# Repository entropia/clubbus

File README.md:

EDEN
====

EDEN is Entropia's home automation project. More information can be found in our [wiki](https://entropia.de/Clubbus).

Stuff will be publicly released here when it's ready.

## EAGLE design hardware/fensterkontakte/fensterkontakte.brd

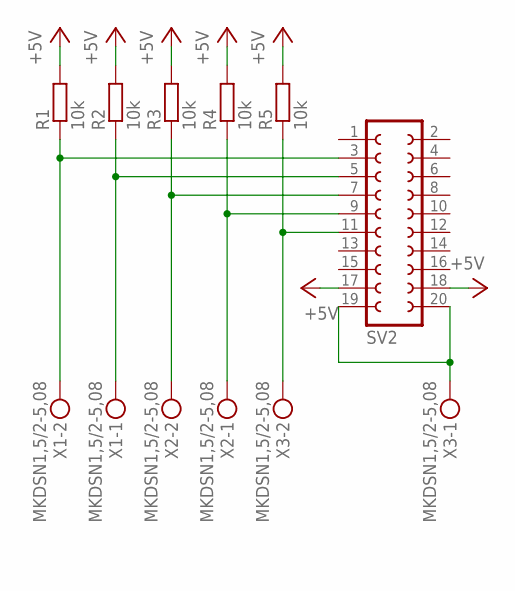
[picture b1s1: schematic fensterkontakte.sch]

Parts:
R1, R2, R3, R4, R5: 10k; M0805
SV2: FE10-2
X1, X2, X3: MKDSN1,5/2-5,08

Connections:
+5V: R1.2, R2.2, R3.2, R4.2, R5.2, SV2.17, SV2.18
GND: SV2.19, SV2.20, X3.1
unnamed: R1.1, SV2.3, X1.2
unnamed: R2.1, SV2.5, X1.1
unnamed: R3.1, SV2.7, X2.2
unnamed: R4.1, SV2.9, X2.1
unnamed: R5.1, SV2.11, X3.2

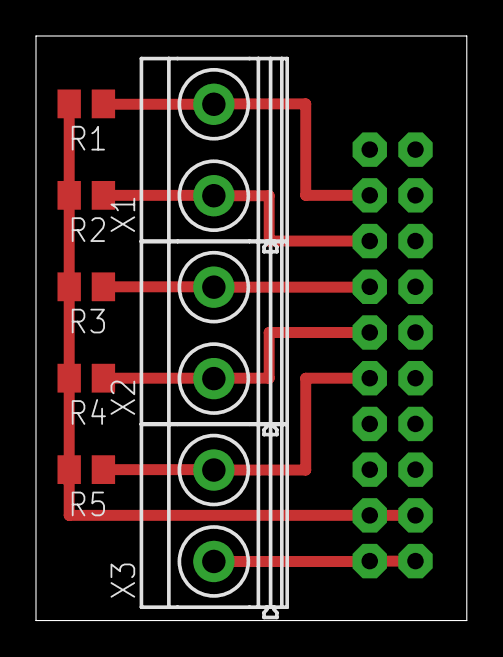
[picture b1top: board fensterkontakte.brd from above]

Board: 2 copper layers, 23.9 x 32.5 mm, 9 parts (1 on the bottom side), 7 nets.

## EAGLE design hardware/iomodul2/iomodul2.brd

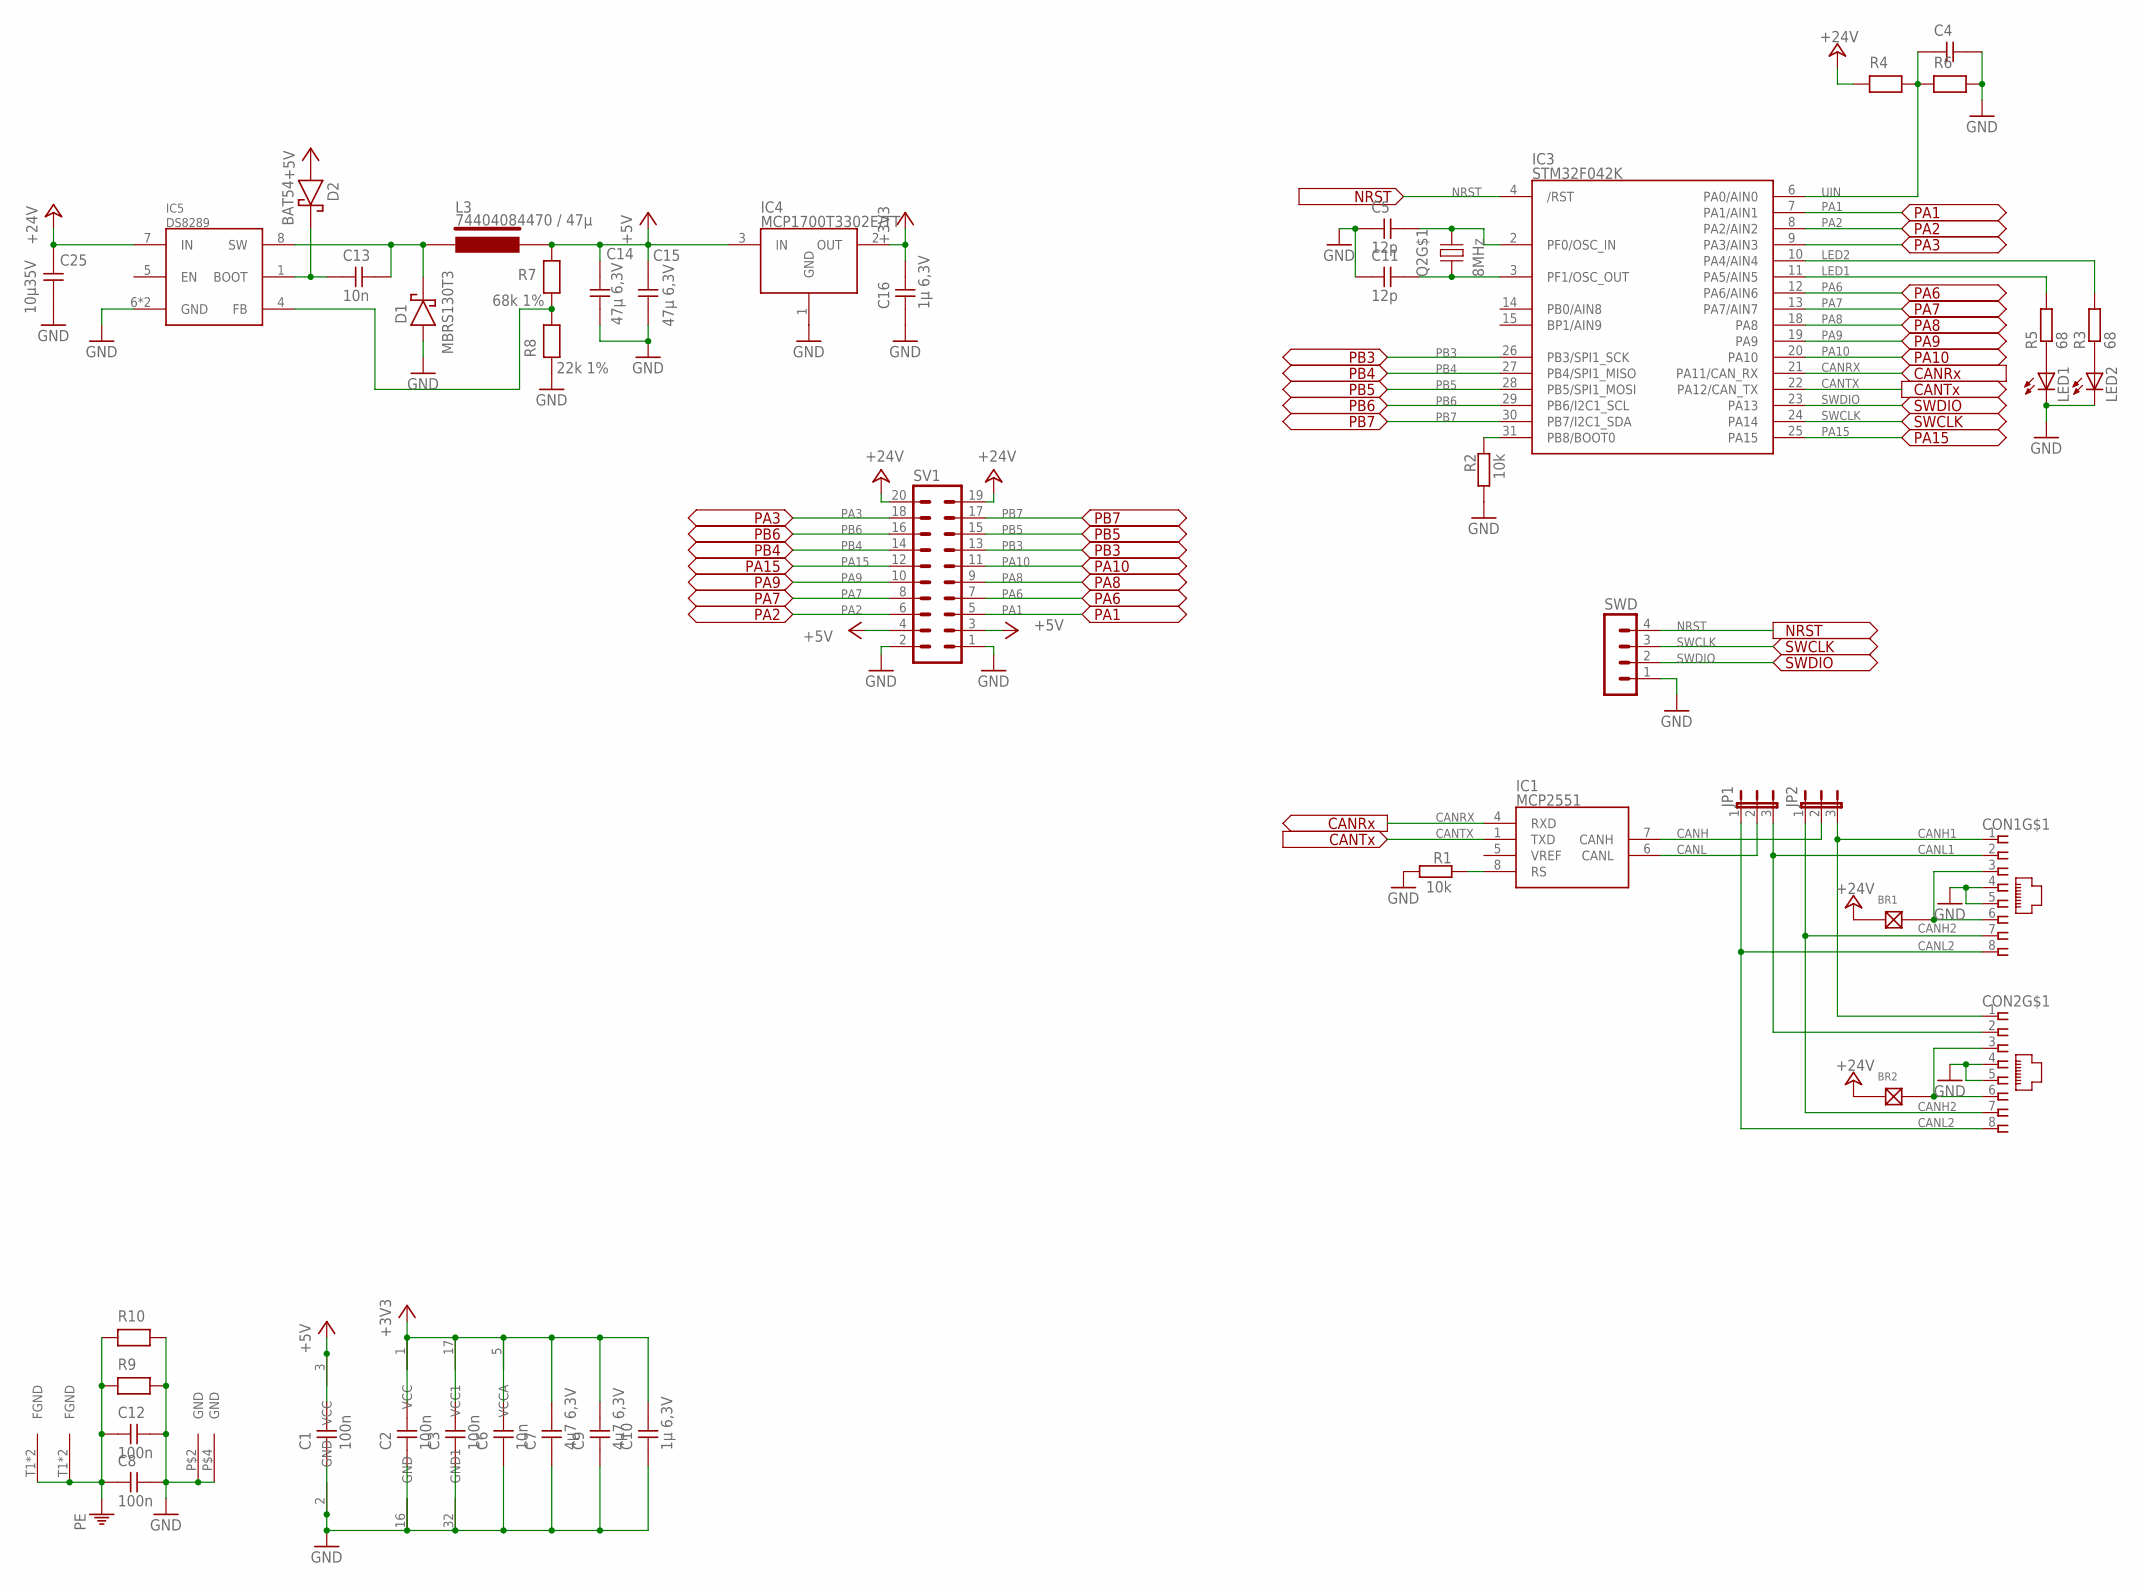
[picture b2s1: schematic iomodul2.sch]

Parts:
BR1, BR2: LÖTBRÜCKE-S; LÖTBRÜCKE
C1, C2, C3, C8, C12: 100n; 0603REFLOW
C4: CAP0603R; 0603REFLOW
C5, C11: 12p; 0603REFLOW
C6, C13: 10n; 0603REFLOW
C7, C9: 4µ7 6,3V; 0603REFLOW
C10, C16: 1µ 6,3V; 0603REFLOW
C14, C15: 47µ 6,3V; 1210
C25: 10µ35V; 1206
CON1, CON2: MEBP_8-8G; MEBP
D1: MBRS130T3; SMB
D2: BAT54; SOT23/32
IC1: MCP2551; SO-8
IC3: STM32F042K; LQFP32
IC4: MCP1700T3302E/TT; SOT23
IC5: DS8289; SO8-POWERPAD
JP1, JP2: JP2E; JP2
L3: 74404084470 / 47µ; WE-LQS
LED1, LED2: LEDCHIPLED_0603; CHIPLED_0603
Q2: 8MHz; MT-CRYSTAL
R1, R2: 10k; R0603
R3, R5: 68; R0603
R4, R6, R9, R10: RES0603R; 0603REFLOW
R7: 68k 1%; 0603REFLOW
R8: 22k 1%; 0603REFLOW
SV1: MA10-2
SWD: MA04-1

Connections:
+3V3: C2.2, C3.2, C6.2, C7.2, C9.2, C10.2, C16.2, IC3.1 (VCC), IC3.5 (VCCA), IC3.17 (VCC1), IC4.2 (OUT)
+5V: C1.2, C14.2, C15.2, D2.1 (A), IC1.3 (VCC), IC4.3 (IN), L3.P$2, R7.2, SV1.3, SV1.4
+24V: BR1.1, BR2.1, C25.2, IC5.7 (IN), R4.1, SV1.19, SV1.20
CANH: IC1.7 (CANH), JP2.2
CANH1: CON1.1, CON2.1, JP2.3
CANH2: CON1.7, CON2.7, JP2.1
CANL: IC1.6 (CANL), JP1.2
CANL1: CON1.2, CON2.2, JP1.3
CANL2: CON1.8, CON2.8, JP1.1
CANRX: IC1.4 (RXD), IC3.21 (PA11/CAN_RX)
CANTX: IC1.1 (TXD), IC3.22 (PA12/CAN_TX)
GND: C1.1, C2.1, C3.1, C4.2, C5.1, C6.1, C7.1, C8.2, C9.1, C10.1, C11.1, C12.2, C14.1, C15.1, C16.1, C25.1, CON1.4, CON1.5, CON2.4, CON2.5, D1.A, IC1.2 (GND), IC3.16 (GND), IC3.32 (GND1), IC4.1 (GND), IC5.6 (GND), IC5.TP (GND), LED1.C, LED2.C, Q2.P$2 (GND), Q2.P$4 (GND), R1.2, R2.2, R6.2, R8.1, R9.2, R10.2, SV1.1, SV1.2, SWD.1
LED1: IC3.11 (PA5/AIN5), R5.2
LED2: IC3.10 (PA4/AIN4), R3.2
unnamed: IC1.8 (RS), R1.1
unnamed: BR1.2, CON1.3, CON1.6
unnamed: LED2.A, R3.1
unnamed: C11.2, IC3.3 (PF1/OSC_OUT), Q2.P$1 (1)
unnamed: C5.2, IC3.2 (PF0/OSC_IN), Q2.P$3 (2)
unnamed: BR2.2, CON2.3, CON2.6
unnamed: LED1.A, R5.1
unnamed: C13.1, D2.3 (K), IC5.1 (BOOT)
unnamed: C13.2, D1.K, IC5.8 (SW), L3.P$1
unnamed: IC3.31 (PB8/BOOT0), R2.1
unnamed: IC5.4 (FB), R7.1, R8.2
NRST: IC3.4 (/RST), SWD.4
PA1: IC3.7 (PA1/AIN1), SV1.5
PA2: IC3.8 (PA2/AIN2), SV1.6
PA3: IC3.9 (PA3/AIN3), SV1.18
PA6: IC3.12 (PA6/AIN6), SV1.7
PA7: IC3.13 (PA7/AIN7), SV1.8
PA8: IC3.18 (PA8), SV1.9
PA9: IC3.19 (PA9), SV1.10
PA10: IC3.20 (PA10), SV1.11
PA15: IC3.25 (PA15), SV1.12
PB3: IC3.26 (PB3/SPI1_SCK), SV1.13
PB4: IC3.27 (PB4/SPI1_MISO), SV1.14
PB5: IC3.28 (PB5/SPI1_MOSI), SV1.15
PB6: IC3.29 (PB6/I2C1_SCL), SV1.16
PB7: IC3.30 (PB7/I2C1_SDA), SV1.17
PE: C8.1, C12.1, CON1.T1 (FGND), CON1.T2 (FGND), CON2.T1 (FGND), CON2.T2 (FGND), R9.1, R10.1
SWCLK: IC3.24 (PA14), SWD.3
SWDIO: IC3.23 (PA13), SWD.2
UIN: C4.1, IC3.6 (PA0/AIN0), R4.2, R6.1

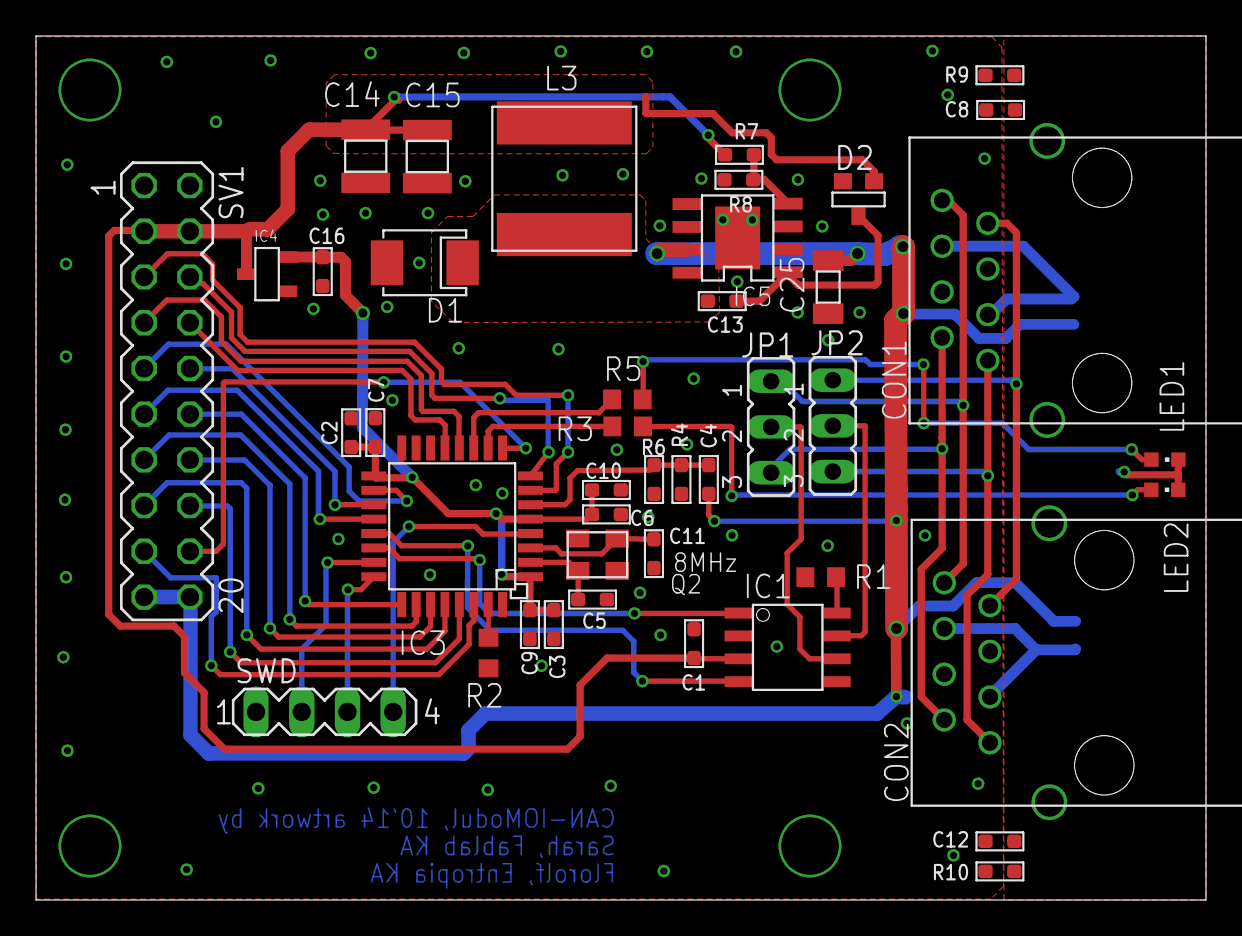
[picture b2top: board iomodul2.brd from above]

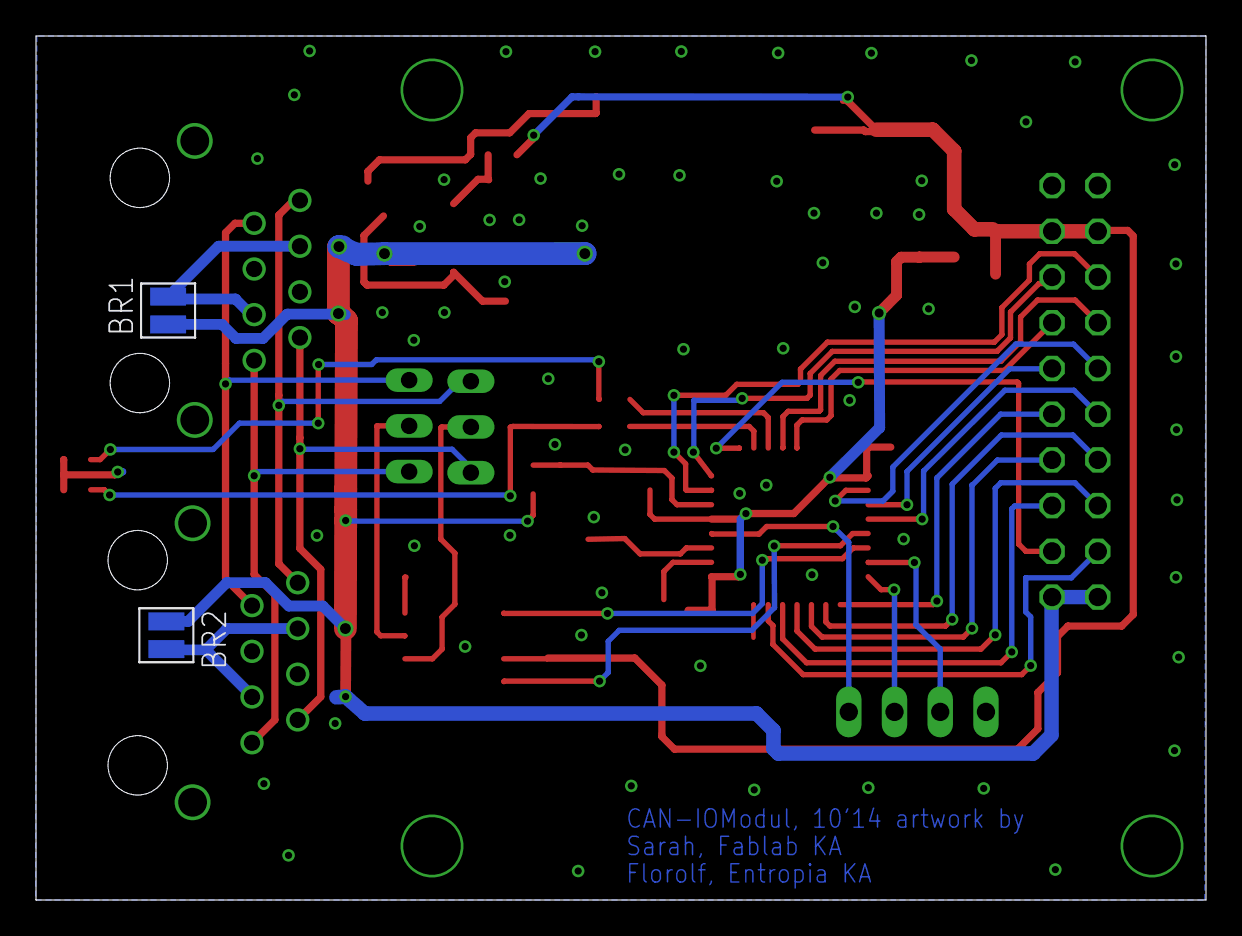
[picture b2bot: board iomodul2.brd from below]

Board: 2 copper layers, 65.0 x 48.0 mm, 45 parts (2 on the bottom side), 44 nets.

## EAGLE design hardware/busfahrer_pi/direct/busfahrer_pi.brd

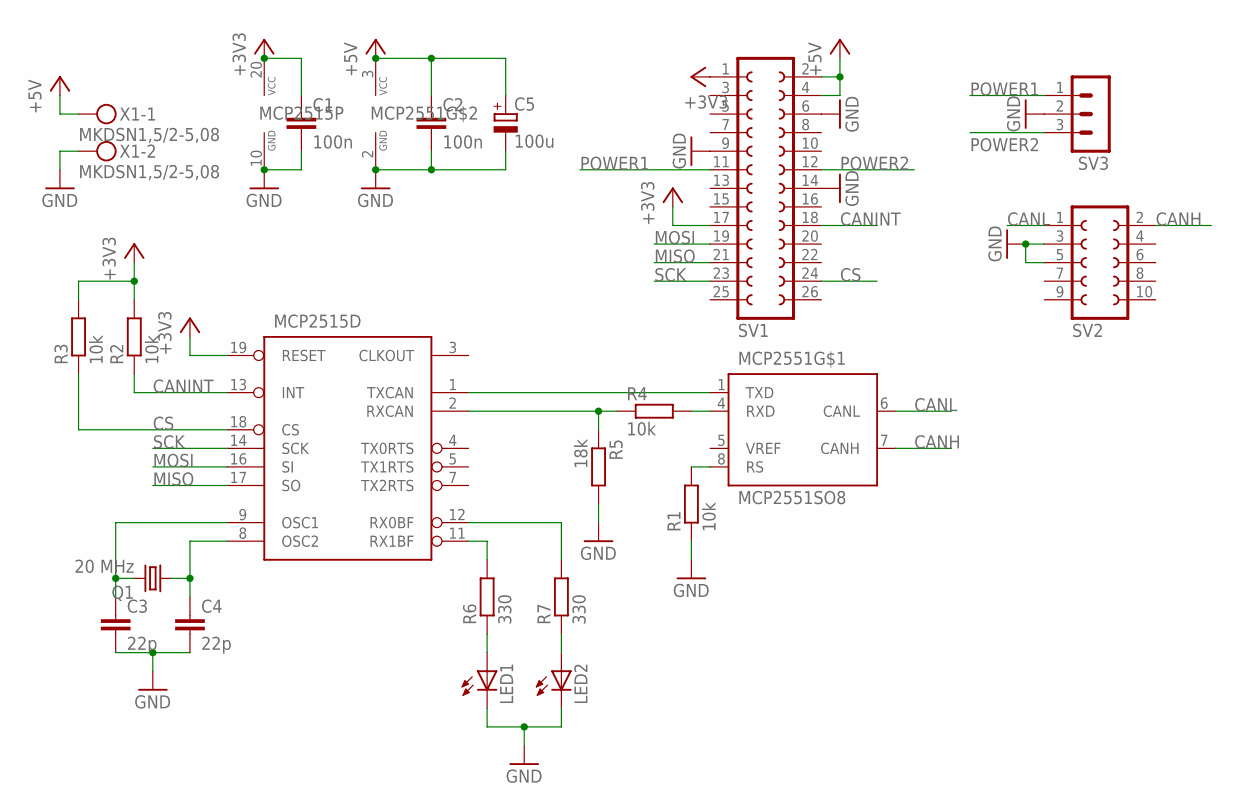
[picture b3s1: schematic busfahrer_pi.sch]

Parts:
C1, C2: 100n; C0805
C3, C4: 22p; C0805
C5: 100u; E2,5-6
LED1, LED2: LEDCHIP-LED0805; CHIP-LED0805
MCP2515: MCP2515ST; TSSOP20
MCP2551: MCP2551SO8; SO08
Q1: 20 MHz; HC49/S
R1, R2, R3, R4: 10k; R0805
R5: 18k; R0805
R6, R7: 330; R0805
SV1: FE13-2
SV2: FE05-2
SV3: MA03-1
X1: MKDSN1,5/2-5,08

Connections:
+3V3: C1.1, MCP2515.19 (RESET), MCP2515.20 (VCC), R2.2, R3.2, SV1.1, SV1.17
+5V: C2.1, C5.+, MCP2551.3 (VCC), SV1.2, SV1.4, X1.1
CANH: MCP2551.7 (CANH), SV2.2
CANINT: MCP2515.13 (INT), R2.1, SV1.18
CANL: MCP2551.6 (CANL), SV2.1
CS: MCP2515.18 (CS), R3.1, SV1.24
GND: C1.2, C2.2, C3.2, C4.2, C5.-, LED1.C, LED2.C, MCP2515.10 (GND), MCP2551.2 (GND), R1.1, R5.2, SV1.6, SV1.9, SV1.14, SV2.3, SV2.5, SV3.2, X1.2
MISO: MCP2515.17 (SO), SV1.21
MOSI: MCP2515.16 (SI), SV1.19
unnamed: MCP2551.8 (RS), R1.2
unnamed: MCP2515.11 (RX1BF), R6.2
unnamed: C4.1, MCP2515.8 (OSC2), Q1.1
unnamed: C3.1, MCP2515.9 (OSC1), Q1.2
unnamed: MCP2515.12 (RX0BF), R7.2
unnamed: LED2.A, R7.1
unnamed: LED1.A, R6.1
POWER1: SV1.11, SV3.1
POWER2: SV1.12, SV3.3
RXCAN: MCP2515.2 (RXCAN), R4.1, R5.1
RXCAN_5V: MCP2551.4 (RXD), R4.2
SCK: MCP2515.14 (SCK), SV1.23
TXCAN: MCP2515.1 (TXCAN), MCP2551.1 (TXD)

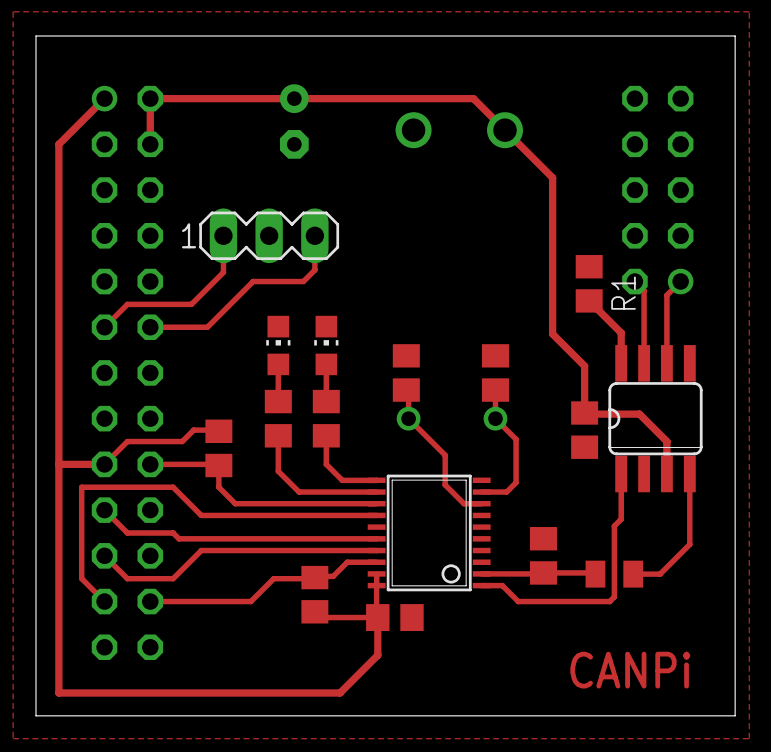
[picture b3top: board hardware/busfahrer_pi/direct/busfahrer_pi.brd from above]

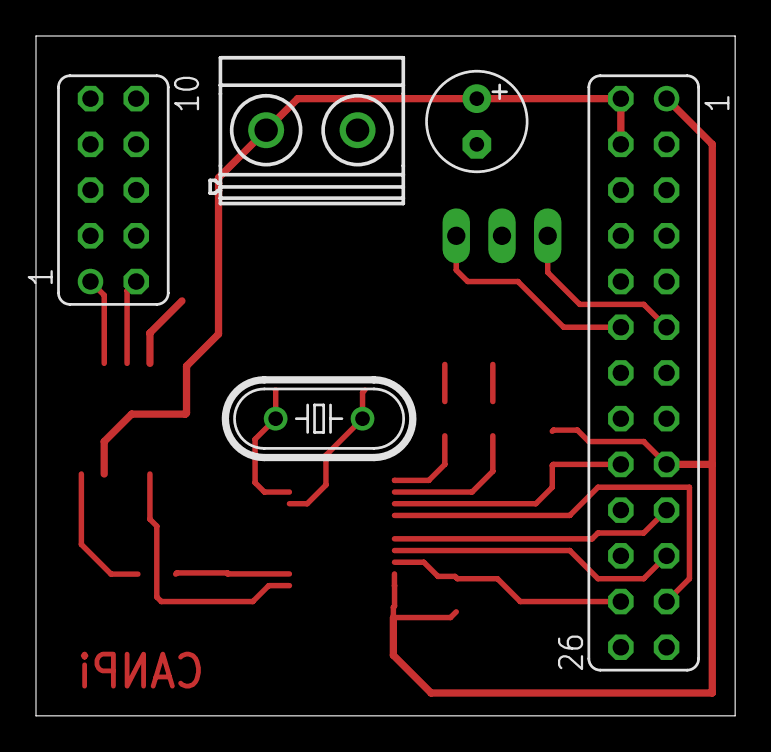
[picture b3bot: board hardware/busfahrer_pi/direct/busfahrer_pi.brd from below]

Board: 2 copper layers, 38.8 x 37.8 mm, 21 parts (5 on the bottom side), 22 nets.

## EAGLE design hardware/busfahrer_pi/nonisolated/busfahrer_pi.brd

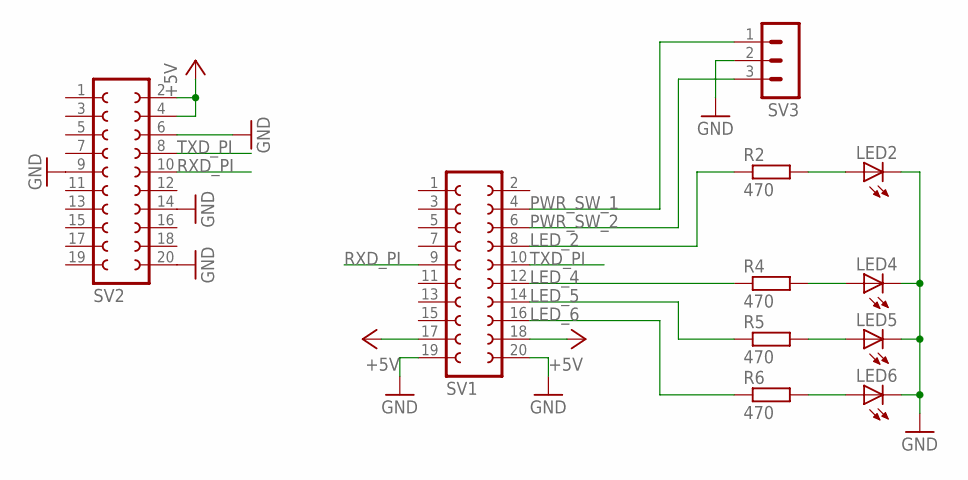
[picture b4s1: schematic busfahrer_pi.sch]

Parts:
LED2, LED4, LED5, LED6: LEDCHIPLED_0805; CHIPLED_0805
R2, R4, R5, R6: 470; R0805
SV1, SV2: FE10-2
SV3: MA03-1

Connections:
+5V: SV1.17, SV1.18, SV2.2, SV2.4
GND: LED2.C, LED4.C, LED5.C, LED6.C, SV1.19, SV1.20, SV2.6, SV2.9, SV2.14, SV2.20, SV3.2
LED_2: R2.1, SV1.8
LED_4: R4.1, SV1.12
LED_5: R5.1, SV1.14
LED_6: R6.1, SV1.16
unnamed: LED2.A, R2.2
unnamed: LED4.A, R4.2
unnamed: LED5.A, R5.2
unnamed: LED6.A, R6.2
PWR_SW_1: SV1.4, SV3.1
PWR_SW_2: SV1.6, SV3.3
RXD_PI: SV1.9, SV2.10
TXD_PI: SV1.10, SV2.8

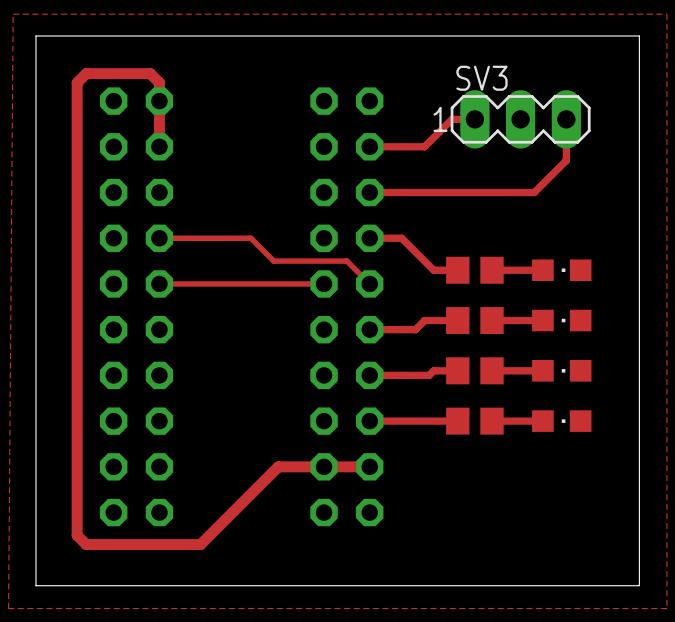
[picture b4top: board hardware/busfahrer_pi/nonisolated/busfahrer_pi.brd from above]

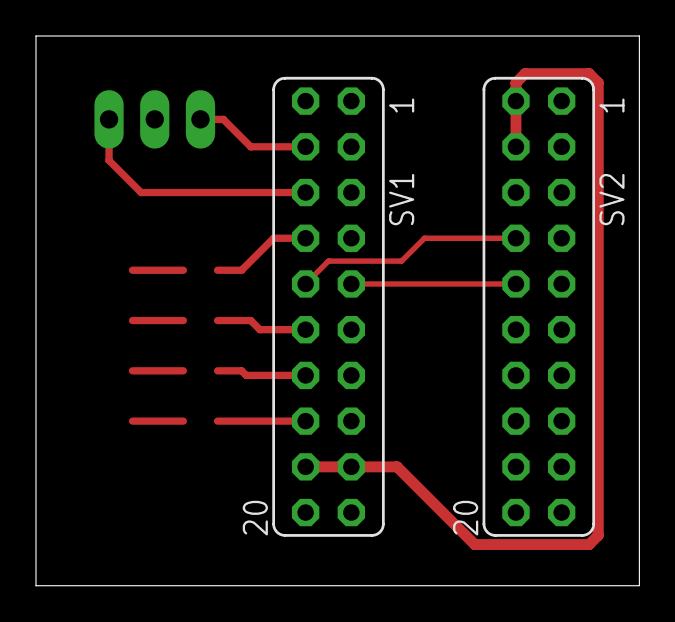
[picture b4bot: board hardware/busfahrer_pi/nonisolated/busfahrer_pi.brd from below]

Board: 2 copper layers, 33.5 x 30.5 mm, 11 parts (2 on the bottom side), 14 nets.

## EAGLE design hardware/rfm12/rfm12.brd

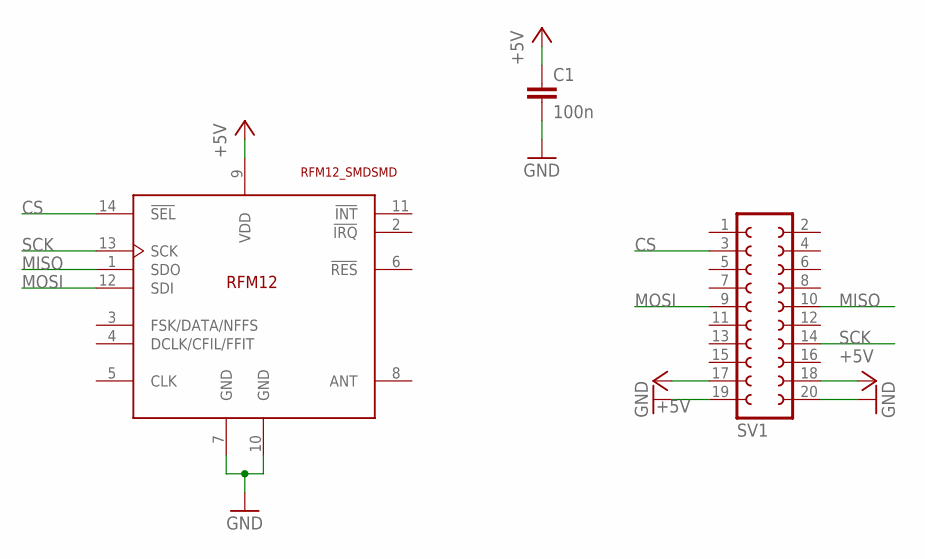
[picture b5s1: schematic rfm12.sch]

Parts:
C1: 100n; C0805
SV1: FE10-2
U$1: RFM12_SMDSMD; RFM12

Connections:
+5V: C1.1, SV1.17, SV1.18, U$1.9 (VDD)
CS: SV1.3, U$1.14 (!SEL)
GND: C1.2, SV1.19, SV1.20, U$1.7 (GND), U$1.10 (GND)
MISO: SV1.10, U$1.1 (SDO)
MOSI: SV1.9, U$1.12 (SDI)
SCK: SV1.14, U$1.13 (SCK)

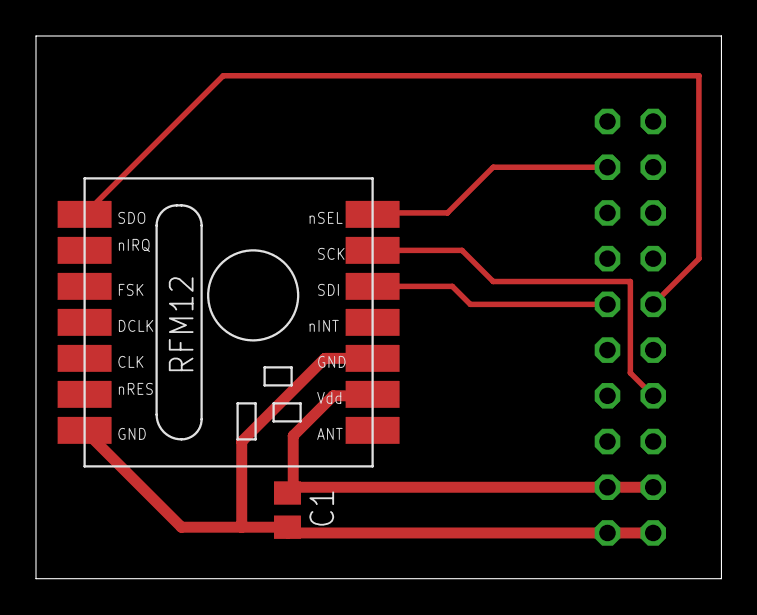
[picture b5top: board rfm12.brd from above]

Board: 2 copper layers, 38.1 x 30.1 mm, 3 parts (1 on the bottom side), 6 nets.

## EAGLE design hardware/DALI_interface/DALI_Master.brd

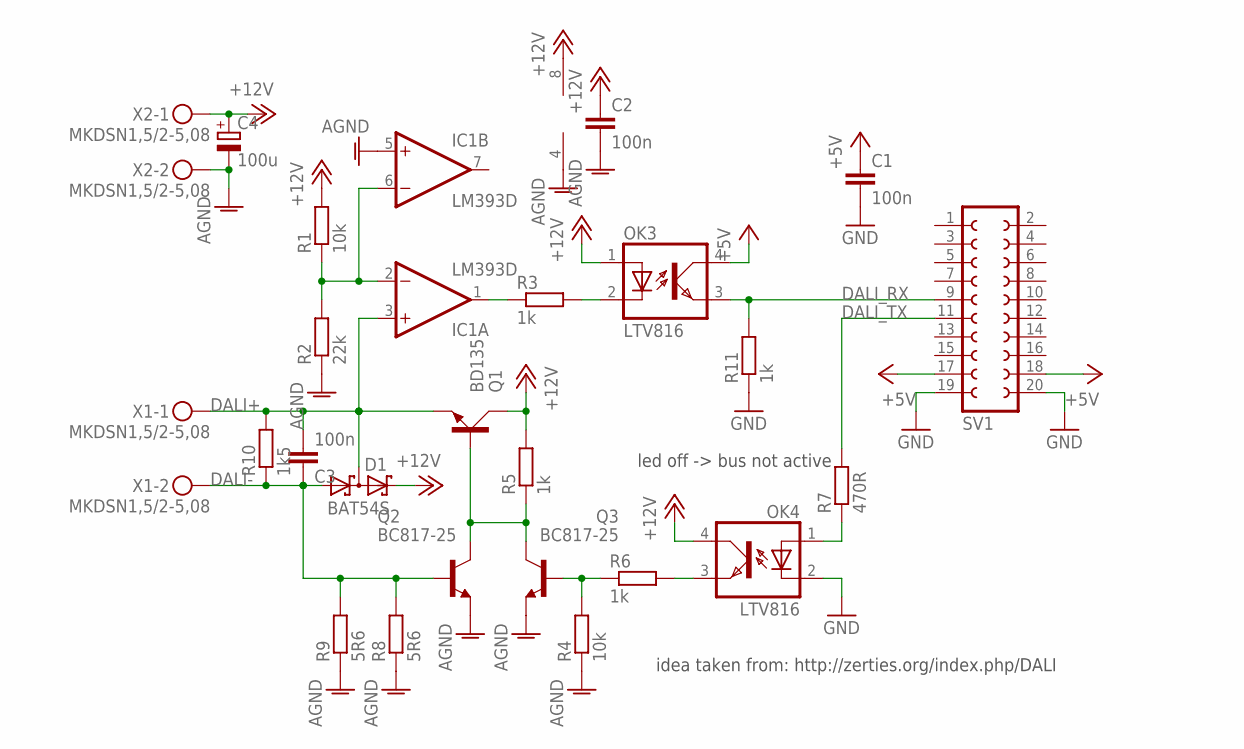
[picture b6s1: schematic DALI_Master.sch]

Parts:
C1, C2, C3: 100n; C0805
C4: 100u; E2,5-6
D1: BAT54S; SOT23
IC1: LM393D; SO08
OK3, OK4: LTV816; DIL04
Q1: BD135; TO126AV
Q2, Q3: BC817-25; SOT23-BEC
R1, R4: 10k; R0805
R2: 22k; R0805
R3, R5, R6, R11: 1k; R0805
R7: 470R; R0805
R8, R9: 5R6; R1206
R10: 1k5; R0805
SV1: FE10-2
X1, X2: MKDSN1,5/2-5,08

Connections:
+5V: C1.1, OK3.4 (COL), SV1.17, SV1.18
+12V: C2.1, C4.+, D1.2 (C2), IC1.8 (V+), OK3.1 (A), OK4.4 (COL), Q1.C, R1.2, R5.2, X2.1
AGND: C2.2, C4.-, IC1.4 (V-), IC1.5 (+IN), Q2.E, Q3.E, R2.1, R4.1, R8.1, R9.1, X2.2
DALI+: C3.2, D1.3 (C1A2), IC1.3 (+IN), Q1.E, R10.2, X1.1
DALI-: C3.1, D1.1 (A1), Q2.B, R8.2, R9.2, R10.1, X1.2
DALI_RX: OK3.3 (EMIT), R11.2, SV1.9
DALI_TX: R7.2, SV1.11
GND: C1.2, OK4.2 (C), R11.1, SV1.19, SV1.20
unnamed: IC1.1 (OUT), R3.1
unnamed: IC1.2 (-IN), IC1.6 (-IN), R1.1, R2.2
unnamed: OK3.2 (C), R3.2
unnamed: Q3.B, R4.2, R6.1
unnamed: OK4.3 (EMIT), R6.2
unnamed: Q1.B, Q2.C, Q3.C, R5.1
unnamed: OK4.1 (A), R7.1

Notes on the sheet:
led off -> bus not active
idea taken from: http://zerties.org/index.php/DALI

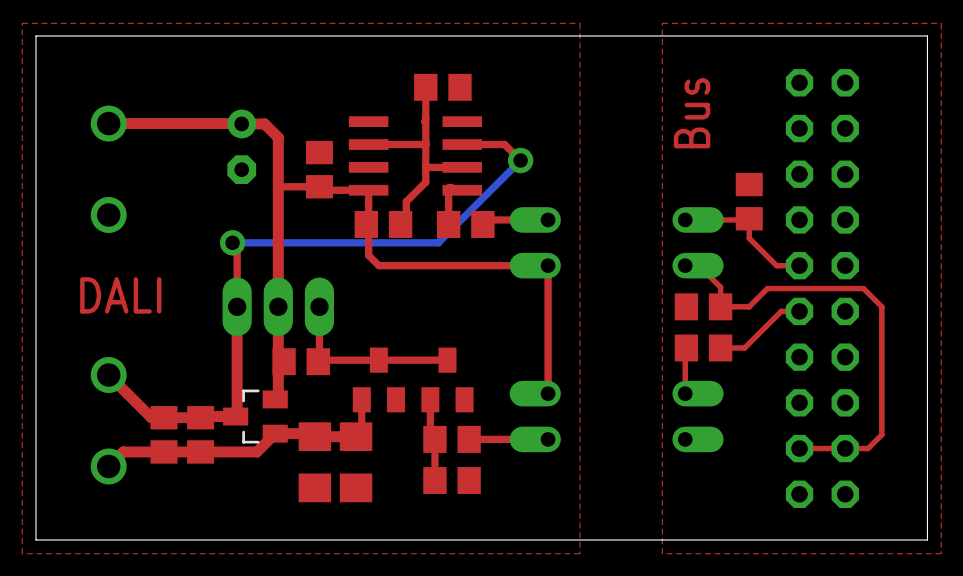
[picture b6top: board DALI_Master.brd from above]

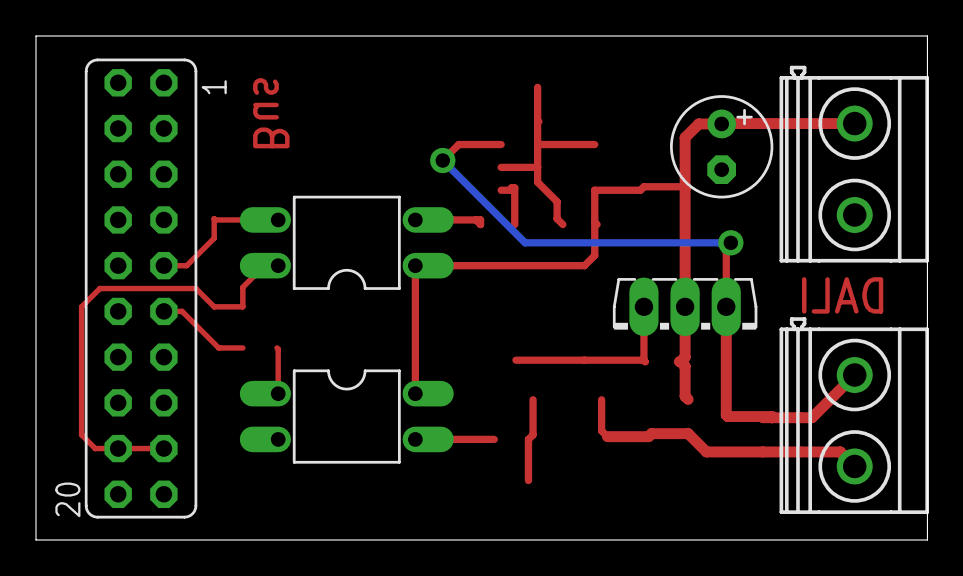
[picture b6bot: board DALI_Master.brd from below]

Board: 2 copper layers, 49.5 x 28.0 mm, 25 parts (7 on the bottom side), 15 nets.

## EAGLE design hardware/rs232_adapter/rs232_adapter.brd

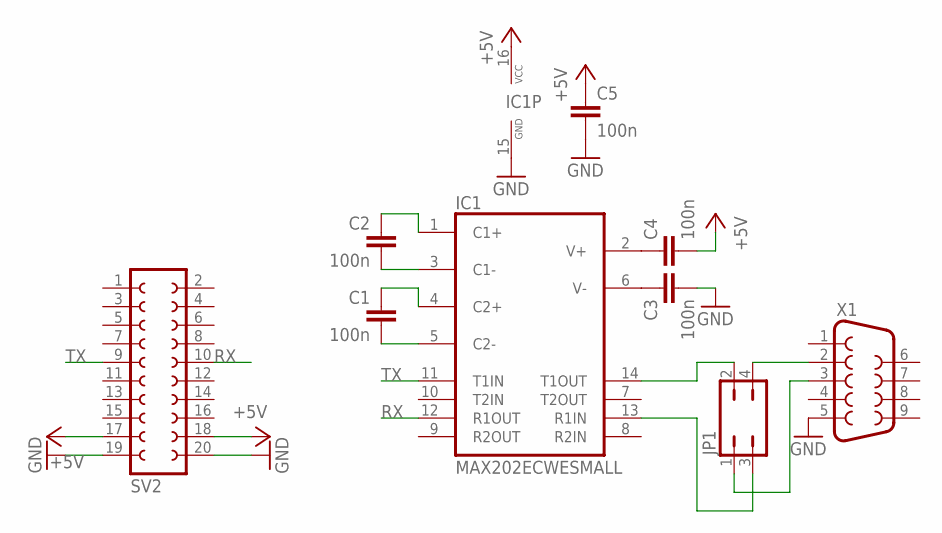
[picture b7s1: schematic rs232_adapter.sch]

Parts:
C1, C2, C3, C4, C5: 100n; C0805
IC1: MAX202ECWESMALL; SO16
JP1: JP2Q
SV2: FE10-2
X1: F09HP

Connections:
+5V: C4.2, C5.1, IC1.16 (VCC), SV2.17, SV2.18
GND: C3.2, C5.2, IC1.15 (GND), SV2.19, SV2.20, X1.5
unnamed: C1.2, IC1.5 (C2-)
unnamed: C1.1, IC1.4 (C2+)
unnamed: C2.2, IC1.3 (C1-)
unnamed: C2.1, IC1.1 (C1+)
unnamed: C3.1, IC1.6 (V-)
unnamed: C4.1, IC1.2 (V+)
unnamed: IC1.14 (T1OUT), JP1.2
unnamed: IC1.13 (R1IN), JP1.3
unnamed: JP1.4, X1.2
unnamed: JP1.1, X1.3
RX: IC1.12 (R1OUT), SV2.10
TX: IC1.11 (T1IN), SV2.9

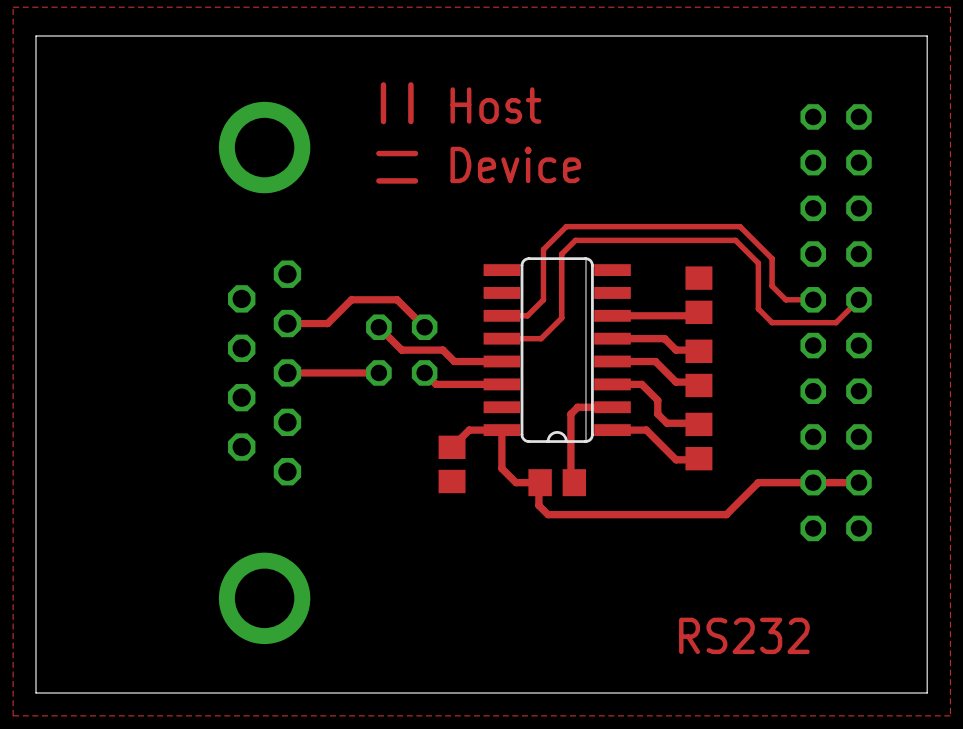
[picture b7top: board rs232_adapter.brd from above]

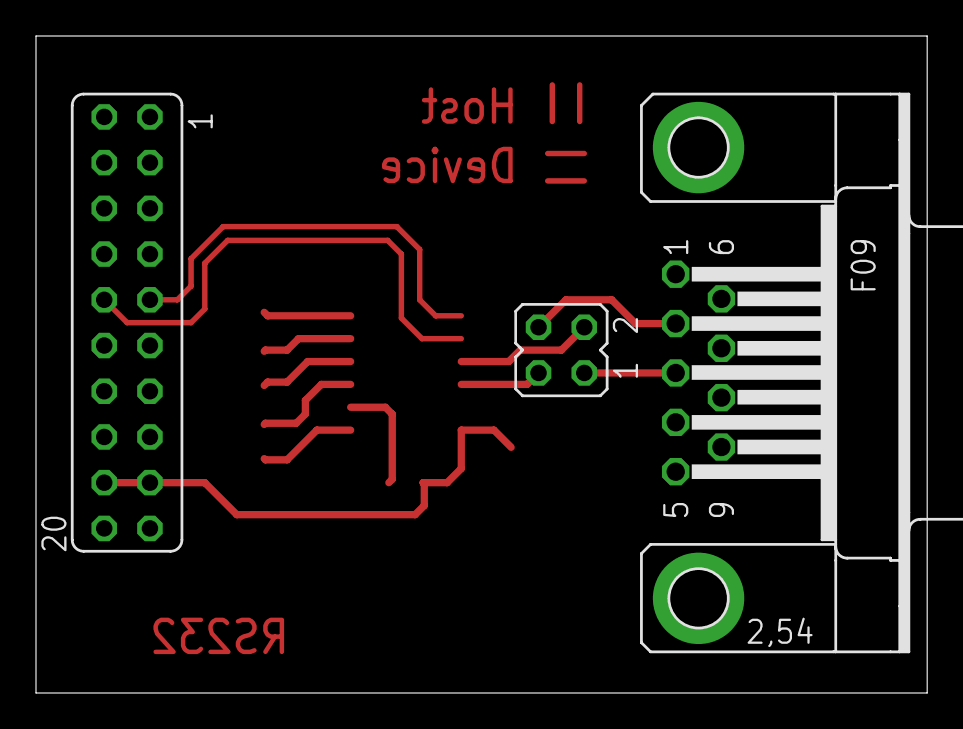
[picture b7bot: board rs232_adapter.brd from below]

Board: 2 copper layers, 49.5 x 36.5 mm, 9 parts (3 on the bottom side), 14 nets.

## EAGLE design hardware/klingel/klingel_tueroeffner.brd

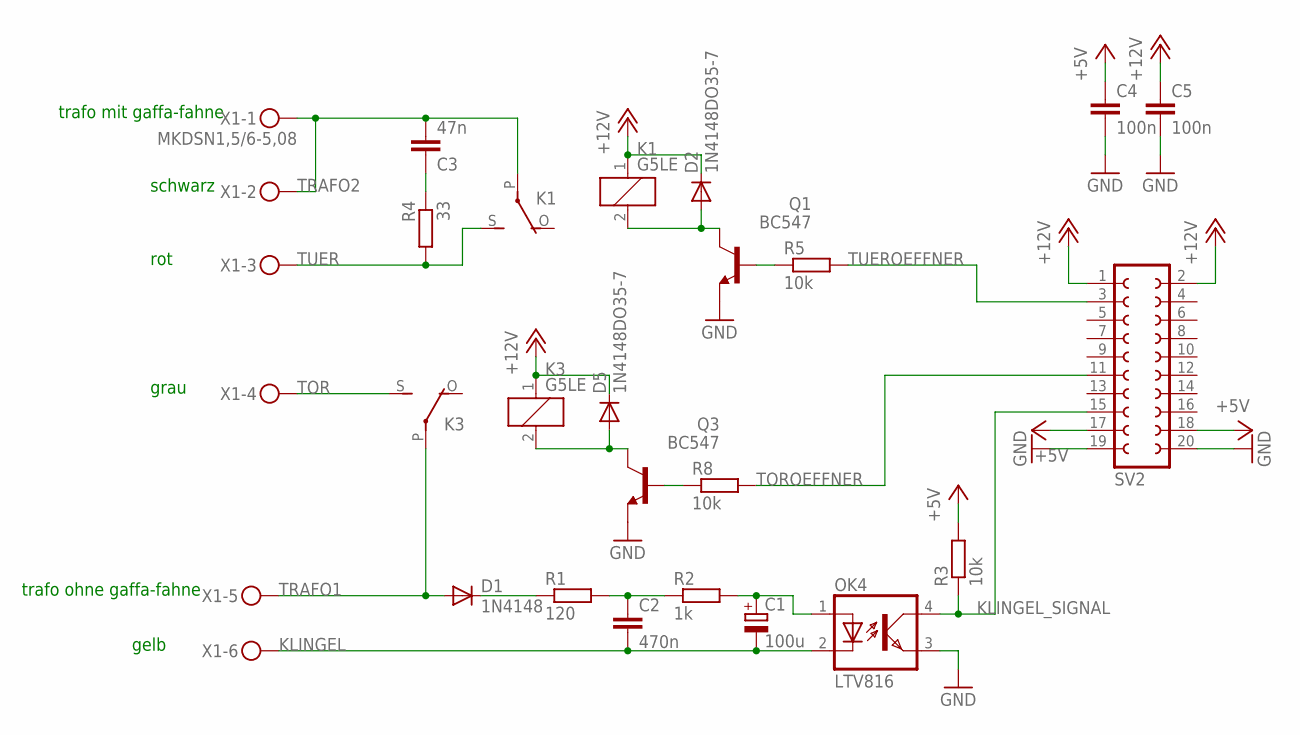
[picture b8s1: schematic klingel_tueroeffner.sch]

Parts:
C1: 100u; E2,5-6
C2: 470n; C050-030X075
C3: 47n; C1206
C4, C5: 100n; C0805
D1: 1N4148; DO35-7
D2, D5: 1N4148DO35-7; DO35-7
K1, K3: G5LE
OK4: LTV816; DIL04
Q1, Q3: BC547; TO92
R1: 120; R1206
R2: 1k; R1206
R3, R8: 10k; R0805
R4: 33; R1206
R5: 10k; 0204/7
SV2: FE10-2
X1: MKDSN1,5/6-5,08

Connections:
+5V: C4.1, R3.2, SV2.17, SV2.18
+12V: C5.1, D2.C, D5.C, K1.1, K3.1, SV2.1, SV2.2
GND: C4.2, C5.2, OK4.3 (EMIT), Q1.1 (E), Q3.1 (E), SV2.19, SV2.20
KLINGEL: C1.-, C2.2, OK4.2 (C), X1.6
KLINGEL_SIGNAL: OK4.4 (COL), R3.1, SV2.15
unnamed: C1.+, OK4.1 (A), R2.2
unnamed: D1.C, R1.1
unnamed: C2.1, R1.2, R2.1
unnamed: C3.1, R4.1
unnamed: Q1.2 (B), R5.1
unnamed: D2.A, K1.2, Q1.3 (C)
unnamed: Q3.2 (B), R8.1
unnamed: D5.A, K3.2, Q3.3 (C)
TOR: K3.S, X1.4
TOROEFFNER: R8.2, SV2.11
TRAFO1: D1.A, K3.P, X1.5
TRAFO2: C3.2, K1.P, X1.1, X1.2
TUER: K1.S, R4.2, X1.3
TUEROEFFNER: R5.2, SV2.3

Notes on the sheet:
trafo mit gaffa-fahne
rot
gelb
grau
schwarz
trafo ohne gaffa-fahne
